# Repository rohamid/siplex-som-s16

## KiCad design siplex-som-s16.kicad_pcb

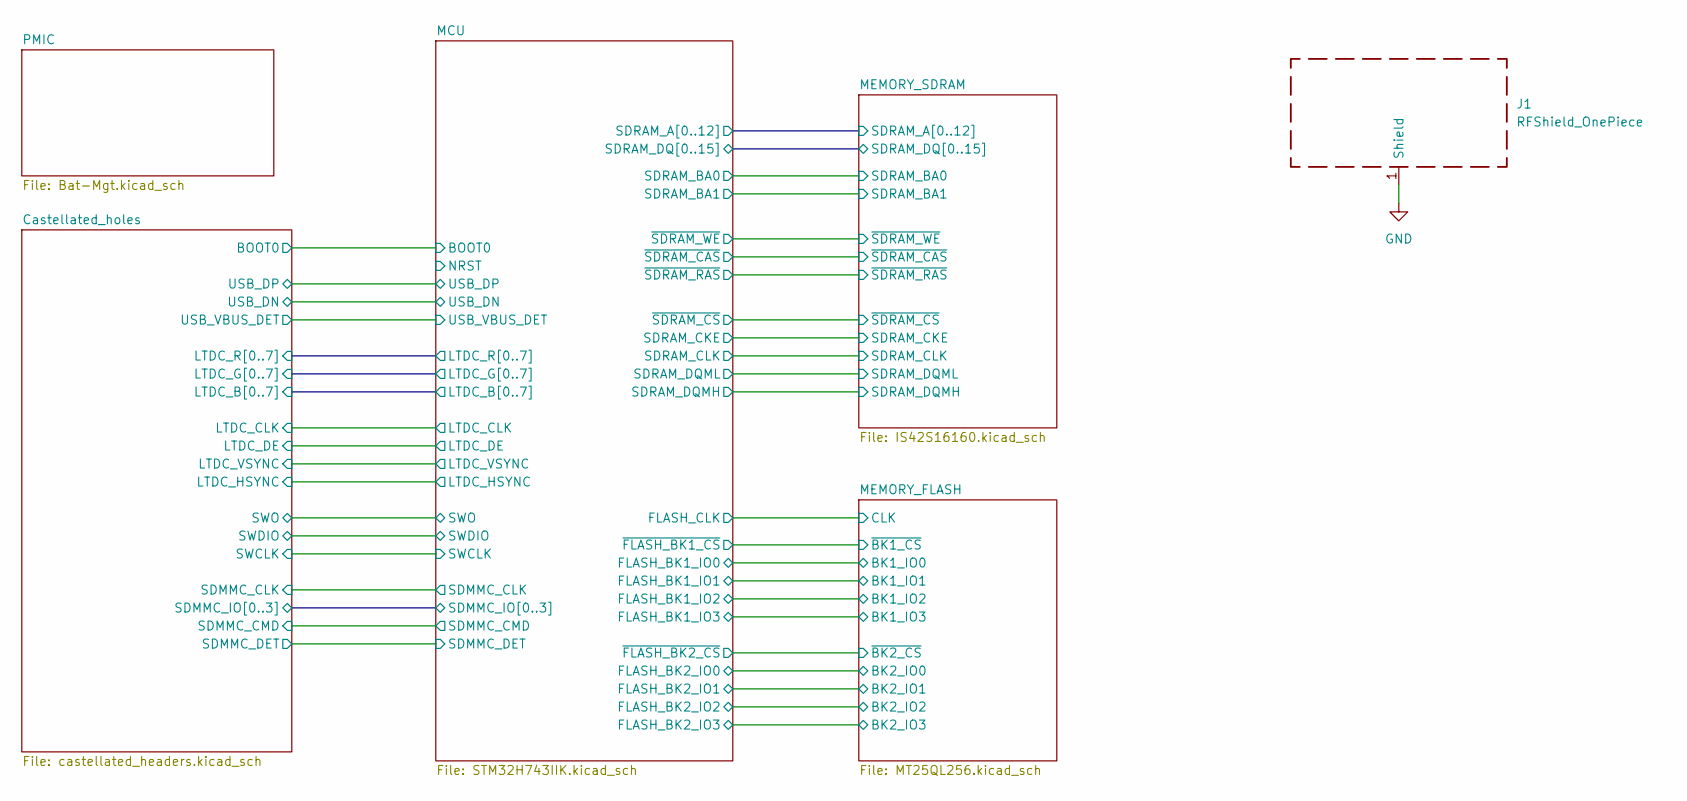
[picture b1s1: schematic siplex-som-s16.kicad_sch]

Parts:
J1: RFShield_OnePiece; Laird_Technologies_BMI-S-103_26.21x26.21mm

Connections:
GND: J1.1 (Shield); also elsewhere on the board

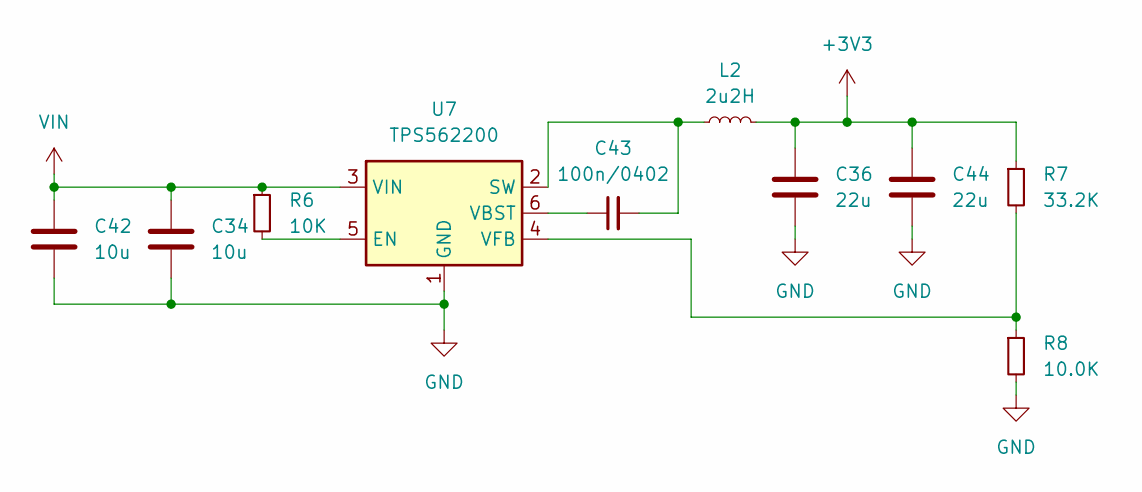
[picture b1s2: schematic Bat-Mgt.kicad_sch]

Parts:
C34, C42: 10u; C_0603_1608Metric; JLCPCB Part # C96446
C36, C44: 22u; C_0603_1608Metric; JLCPCB Part # C59461
C43: 100n/0402; C_0402_1005Metric; JLCPCB Part # C307331
L2: 2u2H; L_0805_2012Metric; JLCPCB Part # C162585
R6: 10K; R_0201_0603Metric; JLCPCB Part # C473048
R7: 33.2K; R_0402_1005Metric; JLCPCB Part # C226998
R8: 10.0K; R_0402_1005Metric; JLCPCB Part # C25804
U7: TPS562200; SOT-23-6; JLCPCB Part # C49757

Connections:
+3V3: C36.1, C44.1, L2.2, R7.1; also elsewhere on the board
GND: C34.2, C36.2, C42.2, C44.2, R8.2, U7.1 (GND); also elsewhere on the board
unnamed: R6.2, U7.5 (EN)
unnamed: C43.2, L2.1, U7.2 (SW)
unnamed: C43.1, U7.6 (VBST)
unnamed: R7.2, R8.1, U7.4 (VFB)
VIN: C34.1, C42.1, R6.1, U7.3 (VIN); also elsewhere on the board

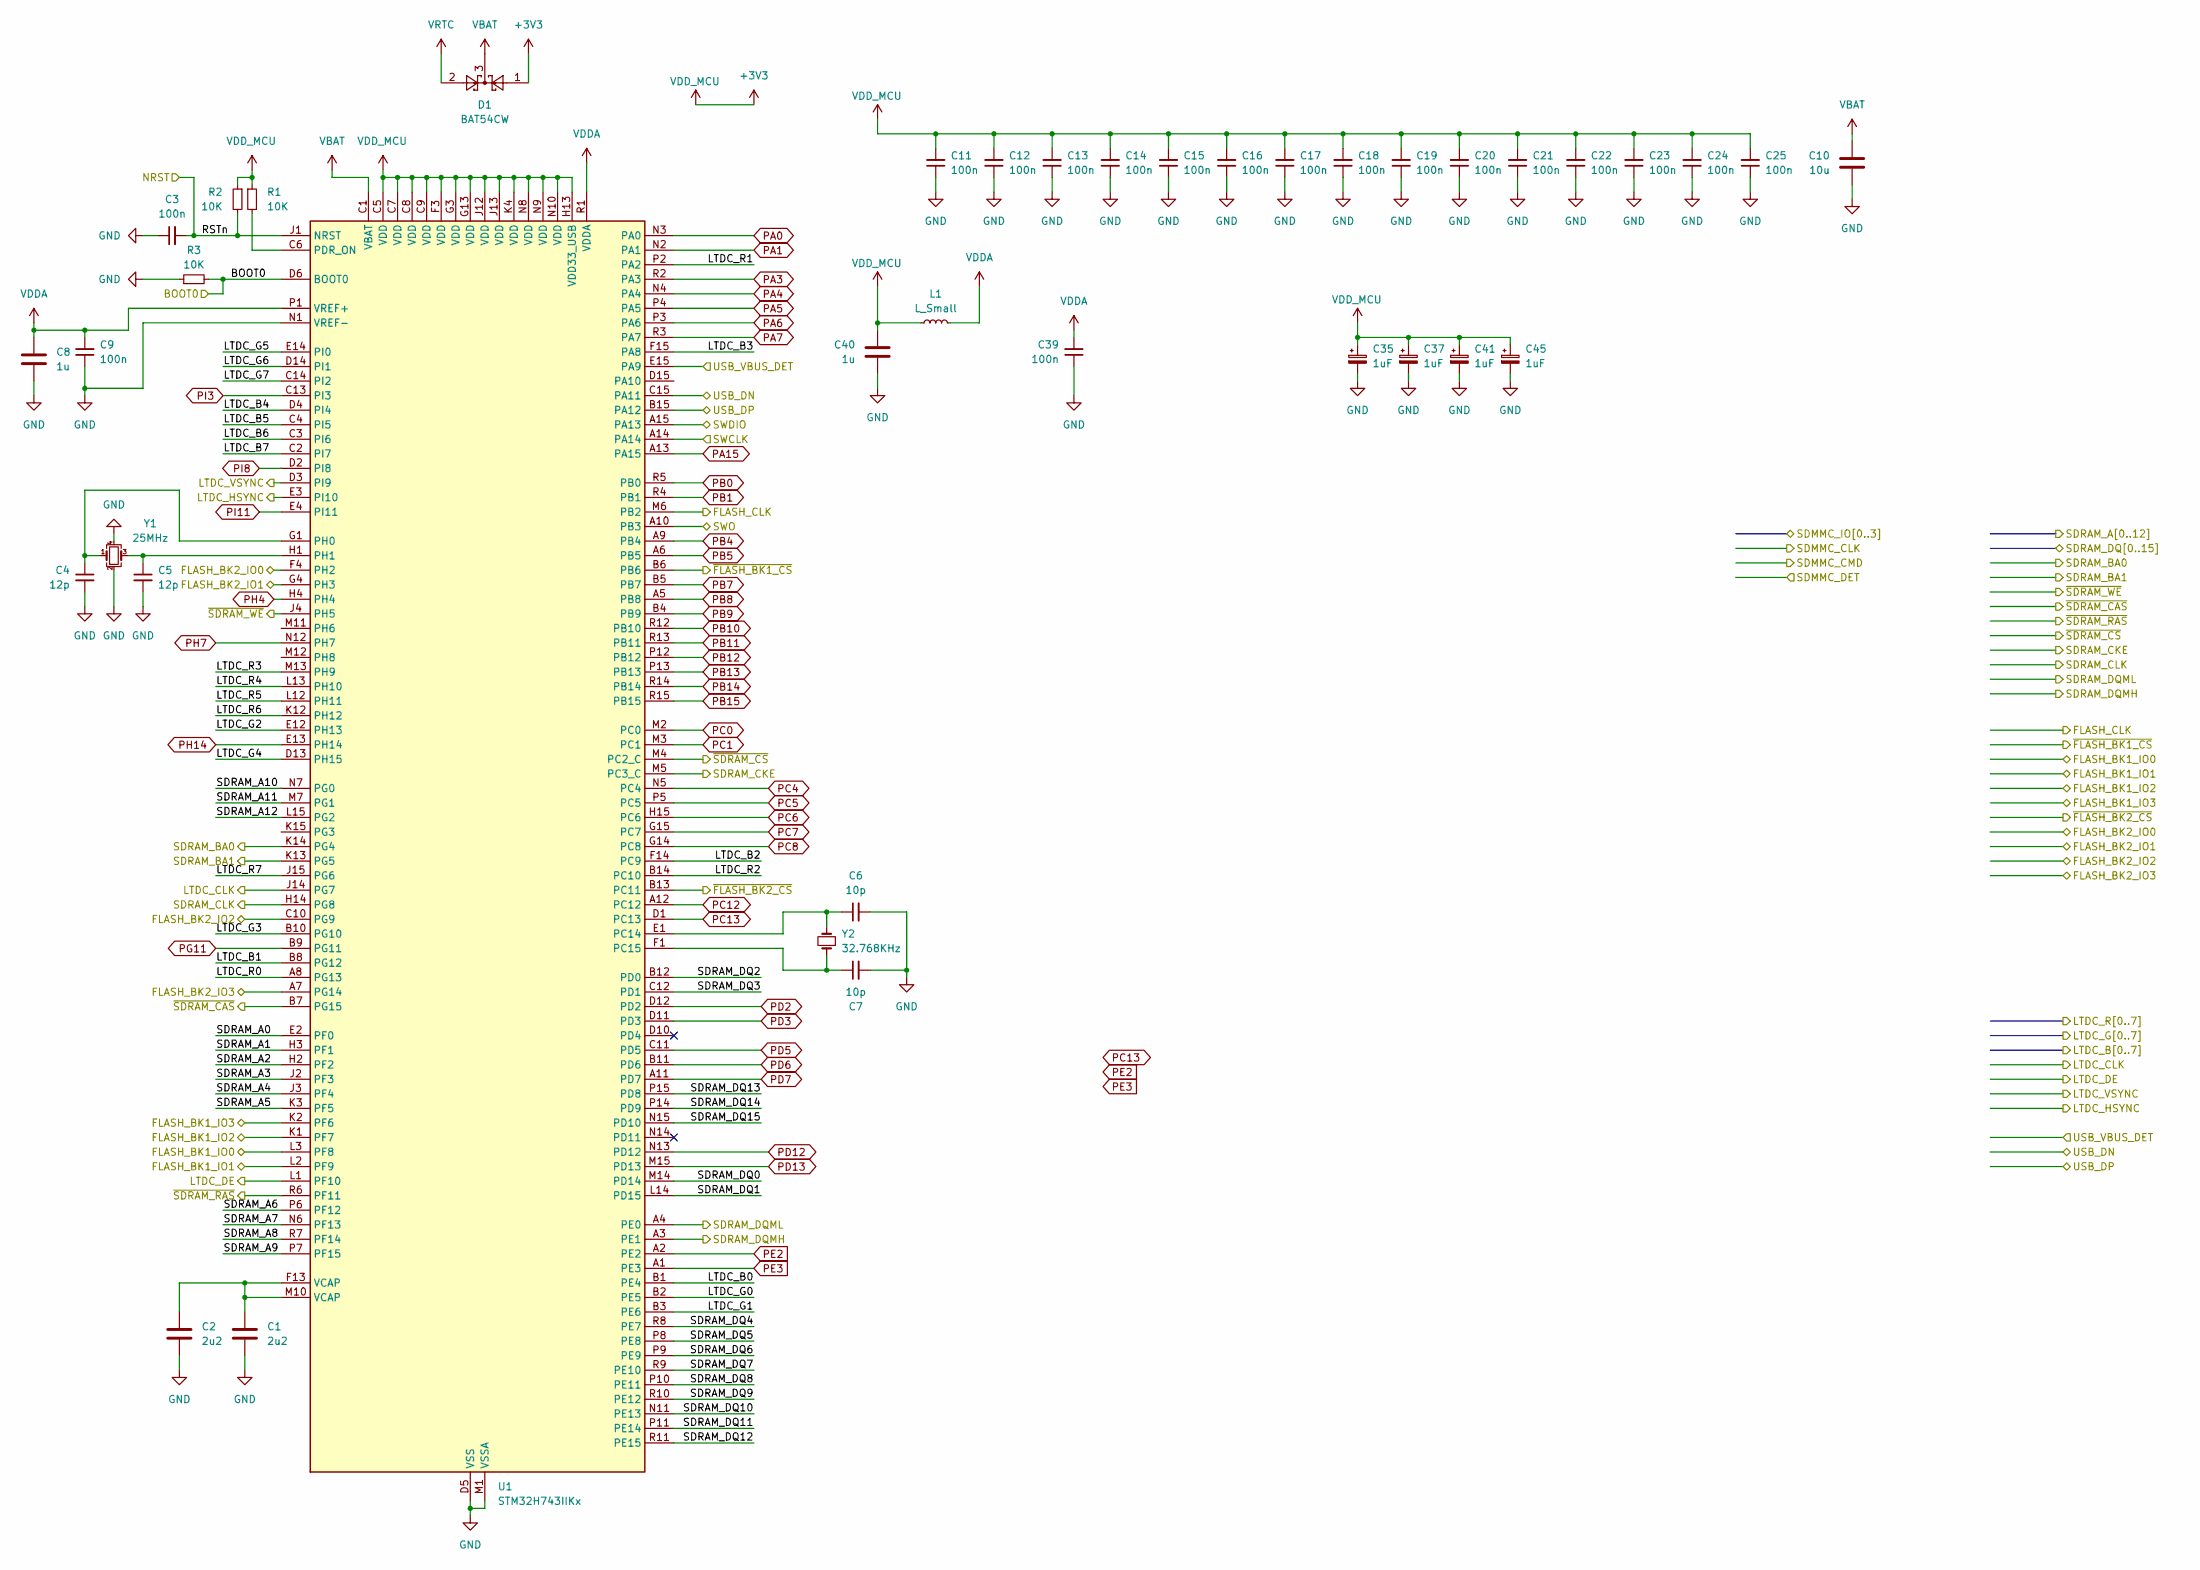
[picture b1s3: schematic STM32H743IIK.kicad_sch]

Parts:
C1, C2: 2u2; C_0402_1005Metric; JLCPCB Part # C12530
C3, C9, C11, C12, C13, C14, C15, C16, C17, C18, C19, C20, C21, C22, C23, C24, C25, C39: 100n; C_0201_0603Metric; JLCPCB Part # C307380
C4, C5: 12p; C_0201_0603Metric; JLCPCB Part # C277478
C6, C7: 10p; C_0201_0603Metric; JLCPCB Part # C76921
C8, C40: 1u; C_0402_1005Metric; JLCPCB Part # C52923
C10: 10u; C_0603_1608Metric; JLCPCB Part # C96446
C35, C37, C41, C45: 1uF; CP_EIA-1608-08_AVX-J
D1: BAT54CW; SOT-23; JLCPCB Part # C37704
L1: L_Small; L_0402_1005Metric; JLCPCB Part # C76891
R1, R2, R3: 10K; R_0201_0603Metric; JLCPCB Part # C473048
U1: STM32H743IIKx; UFBGA-201_10x10mm_Layout15x15_P0.65mm; JLCPCB Part # C129442
Y1: 25MHz; Crystal_SMD_2016-4Pin_2.0x1.6mm; JLCPCB Part # C193187
Y2: 32.768KHz; Crystal_SMD_2012-2Pin_2.0x1.2mm; JLCPCB Part # C99009

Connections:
+3V3: C11.2, C12.2, C13.2, C14.2, C15.2, C16.2, C17.2, C18.2, C19.2, C20.2, C21.2, C22.2, C23.2, C24.2, C25.2, C35.1, C37.1, C40.1, C41.1, C45.1, D1.1, L1.1, R1.1, R2.1, U1.C5 (VDD), U1.C7 (VDD), U1.C8 (VDD), U1.C9 (VDD), U1.F3 (VDD), U1.G3 (VDD), U1.G13 (VDD), U1.H13 (VDD33_USB), U1.J12 (VDD), U1.J13 (VDD), U1.K4 (VDD), U1.N8 (VDD), U1.N9 (VDD), U1.N10 (VDD); also elsewhere on the board
/Castellated_holes/LTDC_B0: U1.B1 (PE4); also elsewhere on the board
/Castellated_holes/LTDC_B1: U1.B8 (PG12); also elsewhere on the board
/Castellated_holes/LTDC_B2: U1.F14 (PC9); also elsewhere on the board
/Castellated_holes/LTDC_B3: U1.F15 (PA8); also elsewhere on the board
/Castellated_holes/LTDC_B4: U1.D4 (PI4); also elsewhere on the board
/Castellated_holes/LTDC_B5: U1.C4 (PI5); also elsewhere on the board
/Castellated_holes/LTDC_B6: U1.C3 (PI6); also elsewhere on the board
/Castellated_holes/LTDC_B7: U1.C2 (PI7); also elsewhere on the board
/Castellated_holes/LTDC_CLK: U1.J14 (PG7); also elsewhere on the board
/Castellated_holes/LTDC_DE: U1.L1 (PF10); also elsewhere on the board
/Castellated_holes/LTDC_G0: U1.B2 (PE5); also elsewhere on the board
/Castellated_holes/LTDC_G1: U1.B3 (PE6); also elsewhere on the board
/Castellated_holes/LTDC_G2: U1.E12 (PH13); also elsewhere on the board
/Castellated_holes/LTDC_G3: U1.B10 (PG10); also elsewhere on the board
/Castellated_holes/LTDC_G4: U1.D13 (PH15); also elsewhere on the board
/Castellated_holes/LTDC_G5: U1.E14 (PI0); also elsewhere on the board
/Castellated_holes/LTDC_G6: U1.D14 (PI1); also elsewhere on the board
/Castellated_holes/LTDC_G7: U1.C14 (PI2); also elsewhere on the board
/Castellated_holes/LTDC_HSYNC: U1.E3 (PI10); also elsewhere on the board
/Castellated_holes/LTDC_R0: U1.A8 (PG13); also elsewhere on the board
/Castellated_holes/LTDC_R1: U1.P2 (PA2); also elsewhere on the board
/Castellated_holes/LTDC_R2: U1.B14 (PC10); also elsewhere on the board
/Castellated_holes/LTDC_R3: U1.M13 (PH9); also elsewhere on the board
/Castellated_holes/LTDC_R4: U1.L13 (PH10); also elsewhere on the board
/Castellated_holes/LTDC_R5: U1.L12 (PH11); also elsewhere on the board
/Castellated_holes/LTDC_R6: U1.K12 (PH12); also elsewhere on the board
/Castellated_holes/LTDC_R7: U1.J15 (PG6); also elsewhere on the board
/Castellated_holes/LTDC_VSYNC: U1.D3 (PI9); also elsewhere on the board
/Castellated_holes/SWCLK: U1.A14; also elsewhere on the board
/Castellated_holes/SWDIO: U1.A15 (PA13); also elsewhere on the board
/Castellated_holes/SWO: U1.A10 (PB3); also elsewhere on the board
/Castellated_holes/USB_DN: U1.C15 (PA11); also elsewhere on the board
/Castellated_holes/USB_DP: U1.B15 (PA12); also elsewhere on the board
/Castellated_holes/USB_VBUS_DET: U1.E15 (PA9); also elsewhere on the board
/MCU/BOOT0: R3.2, U1.D6 (BOOT0); also elsewhere on the board
/MCU/FLASH_BK1_IO0: U1.L3 (PF8); also elsewhere on the board
/MCU/FLASH_BK1_IO1: U1.L2 (PF9); also elsewhere on the board
/MCU/FLASH_BK1_IO2: U1.K1 (PF7); also elsewhere on the board
/MCU/FLASH_BK1_IO3: U1.K2 (PF6); also elsewhere on the board
/MCU/FLASH_BK2_IO0: U1.F4 (PH2); also elsewhere on the board
/MCU/FLASH_BK2_IO1: U1.G4 (PH3); also elsewhere on the board
/MCU/FLASH_BK2_IO2: U1.C10 (PG9); also elsewhere on the board
/MCU/FLASH_BK2_IO3: U1.A7 (PG14); also elsewhere on the board
/MCU/FLASH_CLK: U1.M6 (PB2); also elsewhere on the board
/MCU/RSTn: C3.2, R2.2, U1.J1 (NRST)
/MCU/SDRAM_A0: U1.E2 (PF0); also elsewhere on the board
/MCU/SDRAM_A1: U1.H3 (PF1); also elsewhere on the board
/MCU/SDRAM_A2: U1.H2 (PF2); also elsewhere on the board
/MCU/SDRAM_A3: U1.J2 (PF3); also elsewhere on the board
/MCU/SDRAM_A4: U1.J3 (PF4); also elsewhere on the board
/MCU/SDRAM_A5: U1.K3 (PF5); also elsewhere on the board
/MCU/SDRAM_A6: U1.P6 (PF12); also elsewhere on the board
/MCU/SDRAM_A7: U1.N6 (PF13); also elsewhere on the board
/MCU/SDRAM_A8: U1.R7 (PF14); also elsewhere on the board
/MCU/SDRAM_A9: U1.P7 (PF15); also elsewhere on the board
/MCU/SDRAM_A10: U1.N7 (PG0); also elsewhere on the board
/MCU/SDRAM_A11: U1.M7 (PG1); also elsewhere on the board
/MCU/SDRAM_A12: U1.L15 (PG2); also elsewhere on the board
/MCU/SDRAM_BA0: U1.K14 (PG4); also elsewhere on the board
/MCU/SDRAM_BA1: U1.K13 (PG5); also elsewhere on the board
/MCU/SDRAM_CKE: U1.M5 (PC3_C); also elsewhere on the board
/MCU/SDRAM_CLK: U1.H14 (PG8); also elsewhere on the board
/MCU/SDRAM_DQ0: U1.M14 (PD14); also elsewhere on the board
/MCU/SDRAM_DQ1: U1.L14 (PD15); also elsewhere on the board
/MCU/SDRAM_DQ2: U1.B12 (PD0); also elsewhere on the board
/MCU/SDRAM_DQ3: U1.C12 (PD1); also elsewhere on the board
/MCU/SDRAM_DQ4: U1.R8 (PE7); also elsewhere on the board
/MCU/SDRAM_DQ5: U1.P8 (PE8); also elsewhere on the board
/MCU/SDRAM_DQ6: U1.P9 (PE9); also elsewhere on the board
/MCU/SDRAM_DQ7: U1.R9 (PE10); also elsewhere on the board
/MCU/SDRAM_DQ8: U1.P10 (PE11); also elsewhere on the board
/MCU/SDRAM_DQ9: U1.R10 (PE12); also elsewhere on the board
/MCU/SDRAM_DQ10: U1.N11 (PE13); also elsewhere on the board
/MCU/SDRAM_DQ11: U1.P11 (PE14); also elsewhere on the board
/MCU/SDRAM_DQ12: U1.R11 (PE15); also elsewhere on the board
/MCU/SDRAM_DQ13: U1.P15 (PD8); also elsewhere on the board
/MCU/SDRAM_DQ14: U1.P14 (PD9); also elsewhere on the board
/MCU/SDRAM_DQ15: U1.N15 (PD10); also elsewhere on the board
/MCU/SDRAM_DQMH: U1.A3 (PE1); also elsewhere on the board
/MCU/SDRAM_DQML: U1.A4 (PE0); also elsewhere on the board
/MCU/~FLASH_BK1_CS: U1.B6; also elsewhere on the board
/MCU/~FLASH_BK2_CS: U1.B13 (PC11); also elsewhere on the board
/MCU/~SDRAM_CAS: U1.B7 (PG15); also elsewhere on the board
/MCU/~SDRAM_CS: U1.M4 (PC2_C); also elsewhere on the board
/MCU/~SDRAM_RAS: U1.R6 (PF11); also elsewhere on the board
/MCU/~SDRAM_WE: U1.J4 (PH5); also elsewhere on the board
GND: C1.2, C2.2, C3.1, C4.2, C5.2, C6.2, C7.2, C8.2, C9.1, C10.2, C11.1, C12.1, C13.1, C14.1, C15.1, C16.1, C17.1, C18.1, C19.1, C20.1, C21.1, C22.1, C23.1, C24.1, C25.1, C35.2, C37.2, C39.1, C40.2, C41.2, C45.2, R3.1, U1.D5 (VSS), U1.D7 (VSS), U1.D8 (VSS), U1.D9 (VSS), U1.F2 (VSS), U1.F6 (VSS), U1.F7 (VSS), U1.F8 (VSS), U1.F9 (VSS), U1.F10 (VSS), U1.F12 (VSS), U1.G2 (VSS), U1.G6 (VSS), U1.G7 (VSS), U1.G8 (VSS), U1.G9 (VSS), U1.G10 (VSS), U1.G12 (VSS), U1.H6 (VSS), U1.H7 (VSS), U1.H8 (VSS), U1.H9 (VSS), U1.H10 (VSS), U1.H12 (VSS), U1.J6 (VSS), U1.J7 (VSS), U1.J8 (VSS), U1.J9 (VSS), U1.J10 (VSS), U1.K6 (VSS), U1.K7 (VSS), U1.K8 (VSS), U1.K9 (VSS), U1.K10 (VSS), U1.L4 (VSS), U1.M1 (VSSA), U1.M8 (VSS), U1.M9 (VSS), U1.N1 (VREF-), Y1.2, Y1.4; also elsewhere on the board
unnamed: C1.1, C2.1, U1.F13 (VCAP), U1.M10 (VCAP)
unnamed: C6.1, U1.E1 (PC14), Y2.2
unnamed: C7.1, U1.F1 (PC15), Y2.1
unnamed: R1.2, U1.C6 (PDR_ON)
unnamed: C4.1, U1.G1 (PH0), Y1.1
unnamed: C5.1, U1.H1, Y1.3
PA0: U1.N3 (PA0); also elsewhere on the board
PA1: U1.N2 (PA1); also elsewhere on the board
PA3: U1.R2 (PA3); also elsewhere on the board
PA4: U1.N4 (PA4); also elsewhere on the board
PA5: U1.P4 (PA5); also elsewhere on the board
PA6: U1.P3 (PA6); also elsewhere on the board
PA7: U1.R3 (PA7); also elsewhere on the board
PA15: U1.A13 (PA15); also elsewhere on the board
PB0: U1.R5 (PB0); also elsewhere on the board
PB1: U1.R4 (PB1); also elsewhere on the board
PB4: U1.A9 (PB4); also elsewhere on the board
PB5: U1.A6 (PB5); also elsewhere on the board
PB7: U1.B5 (PB7); also elsewhere on the board
PB8: U1.A5 (PB8); also elsewhere on the board
PB9: U1.B4 (PB9); also elsewhere on the board
PB10: U1.R12 (PB10); also elsewhere on the board
PB11: U1.R13 (PB11); also elsewhere on the board
PB12: U1.P12 (PB12); also elsewhere on the board
PB13: U1.P13 (PB13); also elsewhere on the board
PB14: U1.R14 (PB14); also elsewhere on the board
PB15: U1.R15 (PB15); also elsewhere on the board
PC0: U1.M2 (PC0); also elsewhere on the board
PC1: U1.M3 (PC1); also elsewhere on the board
PC4: U1.N5 (PC4); also elsewhere on the board
PC5: U1.P5 (PC5); also elsewhere on the board
PC6: U1.H15 (PC6); also elsewhere on the board
PC7: U1.G15 (PC7); also elsewhere on the board
PC8: U1.G14 (PC8); also elsewhere on the board
PC12: U1.A12 (PC12); also elsewhere on the board
PC13: U1.D1 (PC13)
PD2: U1.D12 (PD2); also elsewhere on the board
PD3: U1.D11 (PD3); also elsewhere on the board
PD5: U1.C11 (PD5); also elsewhere on the board
PD6: U1.B11 (PD6); also elsewhere on the board
PD7: U1.A11 (PD7); also elsewhere on the board
PD12: U1.N13 (PD12); also elsewhere on the board
PD13: U1.M15 (PD13); also elsewhere on the board
PE2: U1.A2 (PE2)
PE3: U1.A1 (PE3)
PG11: U1.B9 (PG11); also elsewhere on the board
PH4: U1.H4; also elsewhere on the board
PH7: U1.N12 (PH7); also elsewhere on the board
PH14: U1.E13 (PH14); also elsewhere on the board
PI3: U1.C13 (PI3); also elsewhere on the board
PI8: U1.D2 (PI8)
PI11: U1.E4 (PI11)
VBAT: C10.1, D1.3, U1.C1 (VBAT)
VDDA: C8.1, C9.2, C39.2, L1.2, U1.P1 (VREF+), U1.R1 (VDDA)
VRTC: D1.2; also elsewhere on the board

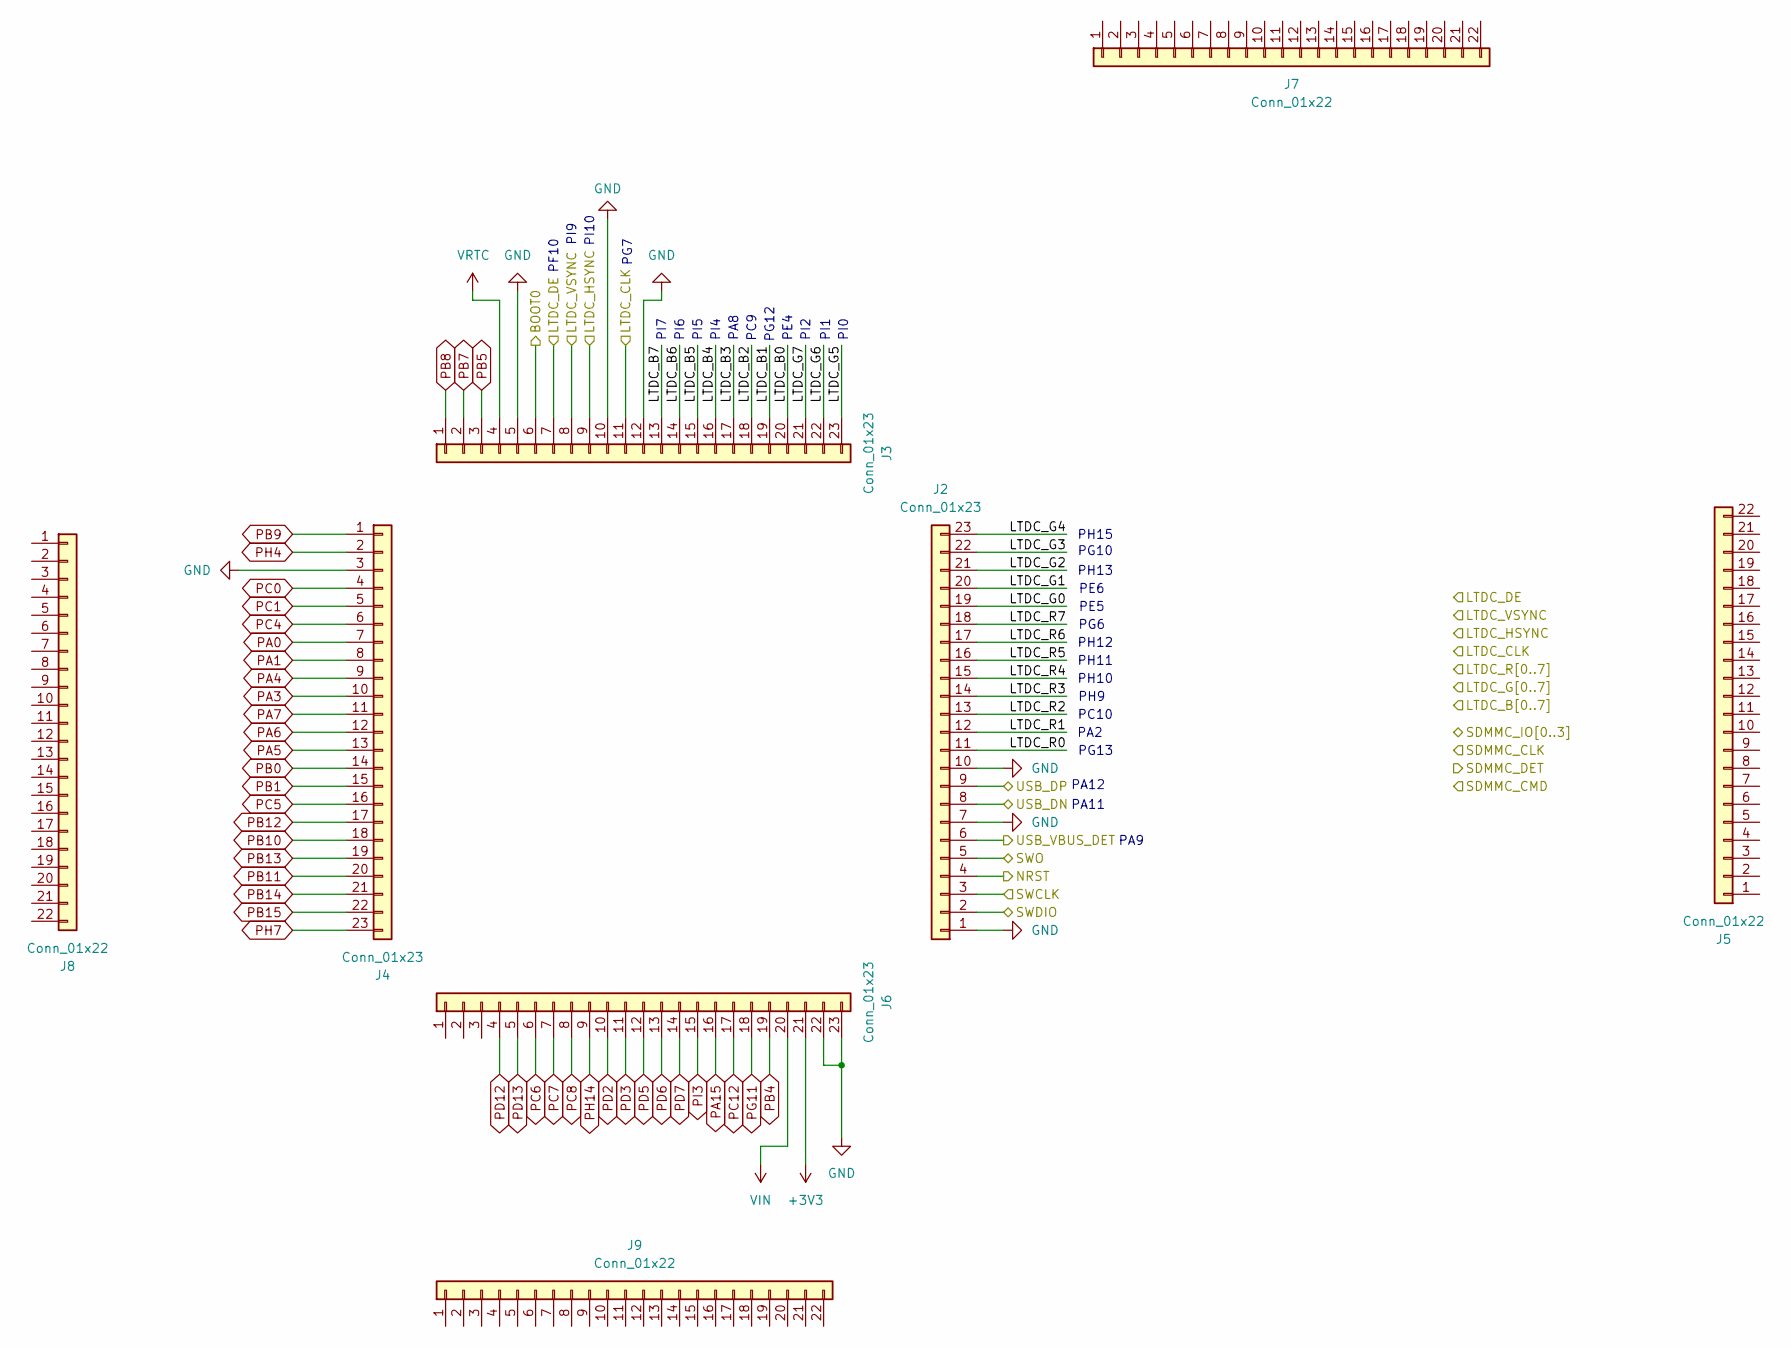
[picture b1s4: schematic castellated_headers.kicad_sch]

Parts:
J2, J3, J4, J6: Conn_01x23; castellated_01x23_P1.2mm
J5, J7, J8, J9: Conn_01x22; castellated_01x22_P1.27mm

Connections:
+3V3: J6.21; also elsewhere on the board
/Castellated_holes/LTDC_B0: J3.20; also elsewhere on the board
/Castellated_holes/LTDC_B1: J3.19; also elsewhere on the board
/Castellated_holes/LTDC_B2: J3.18; also elsewhere on the board
/Castellated_holes/LTDC_B3: J3.17; also elsewhere on the board
/Castellated_holes/LTDC_B4: J3.16; also elsewhere on the board
/Castellated_holes/LTDC_B5: J3.15; also elsewhere on the board
/Castellated_holes/LTDC_B6: J3.14; also elsewhere on the board
/Castellated_holes/LTDC_B7: J3.13; also elsewhere on the board
/Castellated_holes/LTDC_CLK: J3.11; also elsewhere on the board
/Castellated_holes/LTDC_DE: J3.7; also elsewhere on the board
/Castellated_holes/LTDC_G0: J2.19; also elsewhere on the board
/Castellated_holes/LTDC_G1: J2.20; also elsewhere on the board
/Castellated_holes/LTDC_G2: J2.21; also elsewhere on the board
/Castellated_holes/LTDC_G3: J2.22; also elsewhere on the board
/Castellated_holes/LTDC_G4: J2.23; also elsewhere on the board
/Castellated_holes/LTDC_G5: J3.23; also elsewhere on the board
/Castellated_holes/LTDC_G6: J3.22; also elsewhere on the board
/Castellated_holes/LTDC_G7: J3.21; also elsewhere on the board
/Castellated_holes/LTDC_HSYNC: J3.9; also elsewhere on the board
/Castellated_holes/LTDC_R0: J2.11; also elsewhere on the board
/Castellated_holes/LTDC_R1: J2.12; also elsewhere on the board
/Castellated_holes/LTDC_R2: J2.13; also elsewhere on the board
/Castellated_holes/LTDC_R3: J2.14; also elsewhere on the board
/Castellated_holes/LTDC_R4: J2.15; also elsewhere on the board
/Castellated_holes/LTDC_R5: J2.16; also elsewhere on the board
/Castellated_holes/LTDC_R6: J2.17; also elsewhere on the board
/Castellated_holes/LTDC_R7: J2.18; also elsewhere on the board
/Castellated_holes/LTDC_VSYNC: J3.8; also elsewhere on the board
/Castellated_holes/NRST: J2.4
/Castellated_holes/SWCLK: J2.3; also elsewhere on the board
/Castellated_holes/SWDIO: J2.2; also elsewhere on the board
/Castellated_holes/SWO: J2.5; also elsewhere on the board
/Castellated_holes/USB_DN: J2.8; also elsewhere on the board
/Castellated_holes/USB_DP: J2.9; also elsewhere on the board
/Castellated_holes/USB_VBUS_DET: J2.6; also elsewhere on the board
/MCU/BOOT0: J3.6; also elsewhere on the board
GND: J2.1, J2.7, J2.10, J3.5, J3.10, J3.12, J4.3, J6.22, J6.23; also elsewhere on the board
PA0: J4.7; also elsewhere on the board
PA1: J4.8; also elsewhere on the board
PA3: J4.10; also elsewhere on the board
PA4: J4.9; also elsewhere on the board
PA5: J4.13; also elsewhere on the board
PA6: J4.12; also elsewhere on the board
PA7: J4.11; also elsewhere on the board
PA15: J6.16; also elsewhere on the board
PB0: J4.14; also elsewhere on the board
PB1: J4.15; also elsewhere on the board
PB4: J6.19; also elsewhere on the board
PB5: J3.3; also elsewhere on the board
PB7: J3.2; also elsewhere on the board
PB8: J3.1; also elsewhere on the board
PB9: J4.1; also elsewhere on the board
PB10: J4.18; also elsewhere on the board
PB11: J4.20; also elsewhere on the board
PB12: J4.17; also elsewhere on the board
PB13: J4.19; also elsewhere on the board
PB14: J4.21; also elsewhere on the board
PB15: J4.22; also elsewhere on the board
PC0: J4.4; also elsewhere on the board
PC1: J4.5; also elsewhere on the board
PC4: J4.6; also elsewhere on the board
PC5: J4.16; also elsewhere on the board
PC6: J6.6; also elsewhere on the board
PC7: J6.7; also elsewhere on the board
PC8: J6.8; also elsewhere on the board
PC12: J6.17; also elsewhere on the board
PD2: J6.10; also elsewhere on the board
PD3: J6.11; also elsewhere on the board
PD5: J6.12; also elsewhere on the board
PD6: J6.13; also elsewhere on the board
PD7: J6.14; also elsewhere on the board
PD12: J6.4; also elsewhere on the board
PD13: J6.5; also elsewhere on the board
PG11: J6.18; also elsewhere on the board
PH4: J4.2; also elsewhere on the board
PH7: J4.23; also elsewhere on the board
PH14: J6.9; also elsewhere on the board
PI3: J6.15; also elsewhere on the board
VIN: J6.20; also elsewhere on the board
VRTC: J3.4; also elsewhere on the board

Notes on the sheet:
PC10
PI1
PA9
PI6
PG12
PF10
PI7
PI9
PA11
PA12
PG10
PI5
PG7
PI10
PH11
PH15
PI4
PG13
PC9
PH9
PI2
PH13
PA2
PH12
PH10
PA8
PE5
PE4
PI0
PG6
PE6

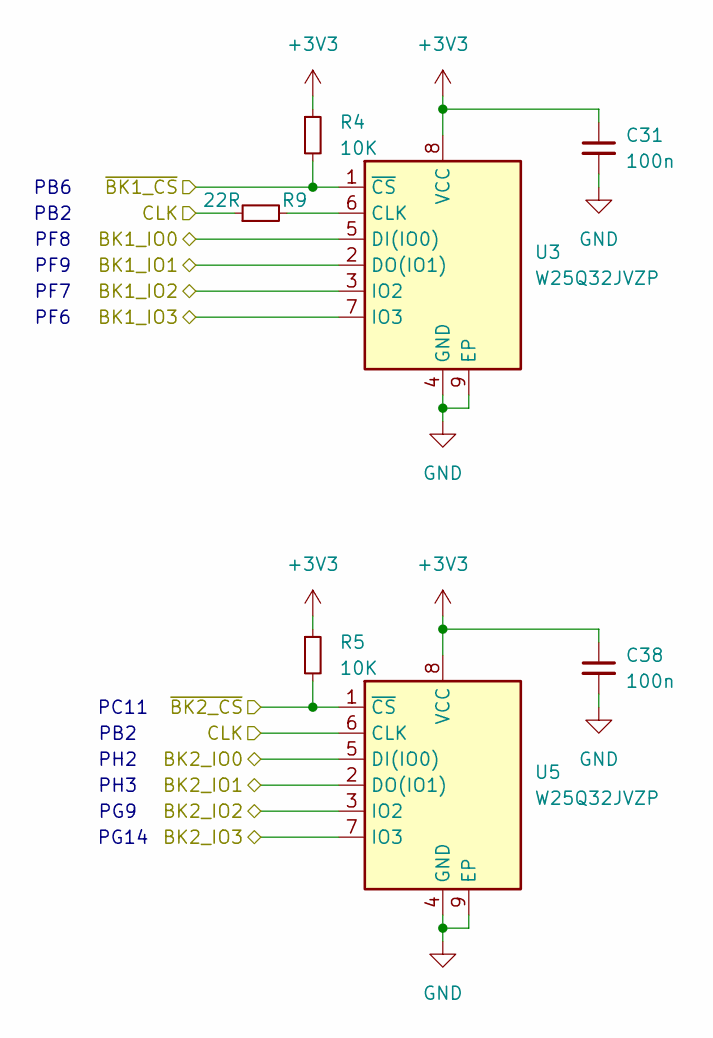
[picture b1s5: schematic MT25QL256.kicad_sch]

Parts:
C31, C38: 100n; C_0201_0603Metric; JLCPCB Part # C307380
R4, R5: 10K; R_0201_0603Metric; JLCPCB Part # C473048
R9: 22R; R_0201_0603Metric; JLCPCB Part # C473048
U3, U5: W25Q32JVZP; SON127P800X600X80-9N; JLCPCB Part # C2986165

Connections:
+3V3: C31.1, C38.1, R4.1, R5.1, U3.8 (VCC), U5.8 (VCC); also elsewhere on the board
/MCU/FLASH_BK1_IO0: U3.5 (DI(IO0)); also elsewhere on the board
/MCU/FLASH_BK1_IO1: U3.2 (DO(IO1)); also elsewhere on the board
/MCU/FLASH_BK1_IO2: U3.3 (IO2); also elsewhere on the board
/MCU/FLASH_BK1_IO3: U3.7 (IO3); also elsewhere on the board
/MCU/FLASH_BK2_IO0: U5.5 (DI(IO0)); also elsewhere on the board
/MCU/FLASH_BK2_IO1: U5.2 (DO(IO1)); also elsewhere on the board
/MCU/FLASH_BK2_IO2: U5.3 (IO2); also elsewhere on the board
/MCU/FLASH_BK2_IO3: U5.7 (IO3); also elsewhere on the board
/MCU/FLASH_CLK: R9.1, U5.6 (CLK); also elsewhere on the board
/MCU/~FLASH_BK1_CS: R4.2, U3.1 (~CS); also elsewhere on the board
/MCU/~FLASH_BK2_CS: R5.2, U5.1 (~CS); also elsewhere on the board
GND: C31.2, C38.2, U3.4 (GND), U3.9 (EP), U5.4 (GND), U5.9 (EP); also elsewhere on the board
unnamed: R9.2, U3.6 (CLK)

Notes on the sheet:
PB6
PB2
PF7
PF8
PG9
PF6
PG14
PH3
PC11
PF9
PH2

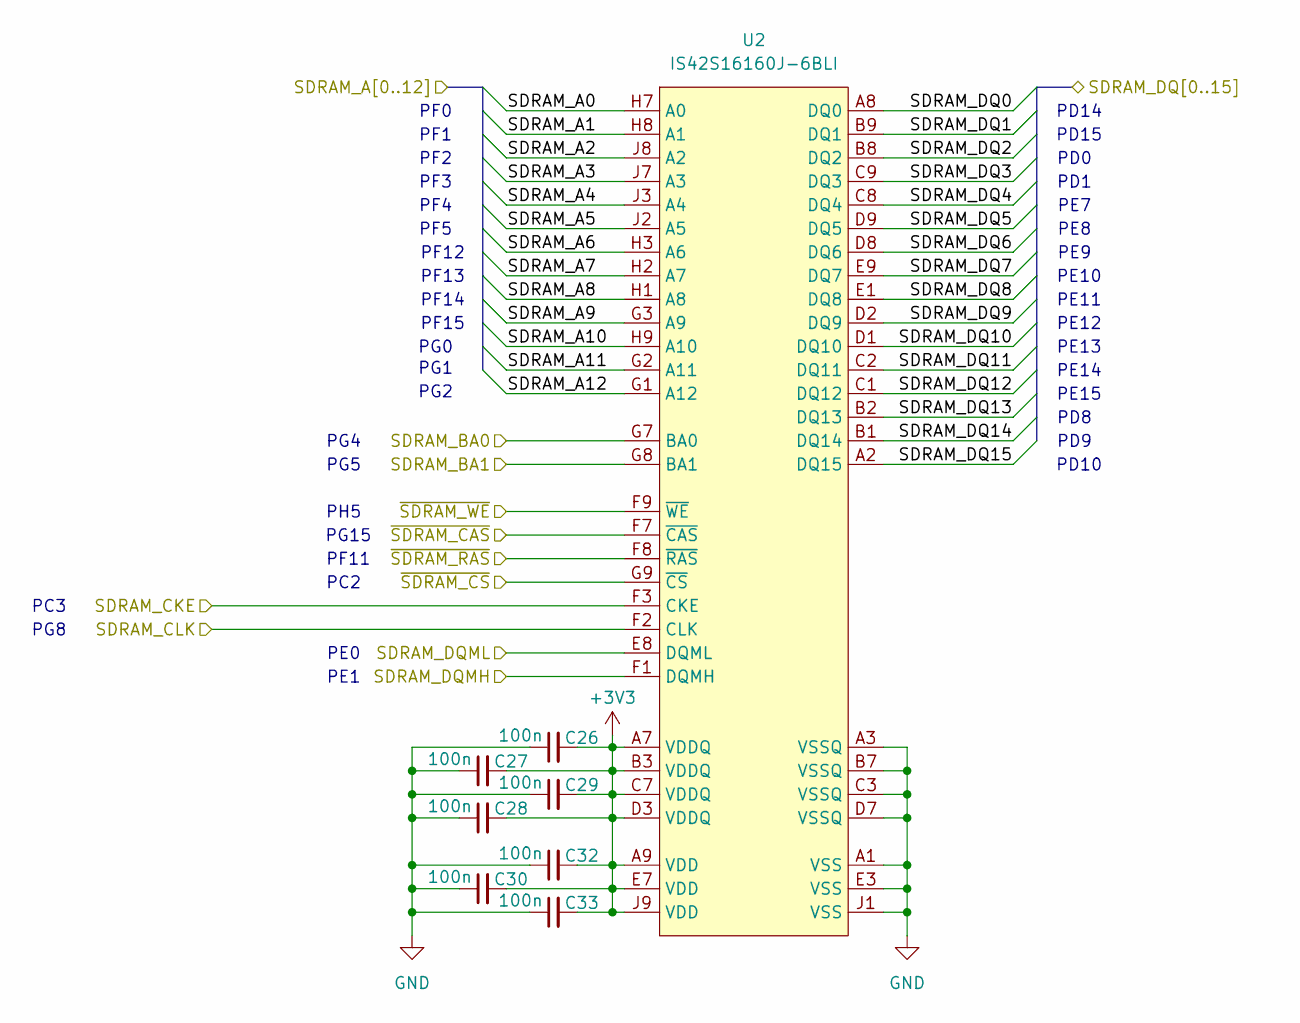
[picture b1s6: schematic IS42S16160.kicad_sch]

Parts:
C26, C27, C28, C29, C30, C32, C33: 100n; C_0201_0603Metric; JLCPCB Part # C307380
U2: IS42S16160J-6BLI; Alliance_TFBGA-54_8x8mm_Layout9x9_P0.8mm; JLCPCB Part # C1348766

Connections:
+3V3: C26.2, C27.2, C28.2, C29.2, C30.2, C32.2, C33.2, U2.A7 (VDDQ), U2.A9 (VDD), U2.B3 (VDDQ), U2.C7 (VDDQ), U2.D3 (VDDQ), U2.E7 (VDD), U2.J9 (VDD); also elsewhere on the board
/MCU/SDRAM_A0: U2.H7 (A0); also elsewhere on the board
/MCU/SDRAM_A1: U2.H8 (A1); also elsewhere on the board
/MCU/SDRAM_A2: U2.J8 (A2); also elsewhere on the board
/MCU/SDRAM_A3: U2.J7 (A3); also elsewhere on the board
/MCU/SDRAM_A4: U2.J3 (A4); also elsewhere on the board
/MCU/SDRAM_A5: U2.J2 (A5); also elsewhere on the board
/MCU/SDRAM_A6: U2.H3 (A6); also elsewhere on the board
/MCU/SDRAM_A7: U2.H2 (A7); also elsewhere on the board
/MCU/SDRAM_A8: U2.H1 (A8); also elsewhere on the board
/MCU/SDRAM_A9: U2.G3 (A9); also elsewhere on the board
/MCU/SDRAM_A10: U2.H9 (A10); also elsewhere on the board
/MCU/SDRAM_A11: U2.G2 (A11); also elsewhere on the board
/MCU/SDRAM_A12: U2.G1 (A12); also elsewhere on the board
/MCU/SDRAM_BA0: U2.G7 (BA0); also elsewhere on the board
/MCU/SDRAM_BA1: U2.G8 (BA1); also elsewhere on the board
/MCU/SDRAM_CKE: U2.F3 (CKE); also elsewhere on the board
/MCU/SDRAM_CLK: U2.F2 (CLK); also elsewhere on the board
/MCU/SDRAM_DQ0: U2.A8 (DQ0); also elsewhere on the board
/MCU/SDRAM_DQ1: U2.B9 (DQ1); also elsewhere on the board
/MCU/SDRAM_DQ2: U2.B8 (DQ2); also elsewhere on the board
/MCU/SDRAM_DQ3: U2.C9 (DQ3); also elsewhere on the board
/MCU/SDRAM_DQ4: U2.C8 (DQ4); also elsewhere on the board
/MCU/SDRAM_DQ5: U2.D9 (DQ5); also elsewhere on the board
/MCU/SDRAM_DQ6: U2.D8 (DQ6); also elsewhere on the board
/MCU/SDRAM_DQ7: U2.E9 (DQ7); also elsewhere on the board
/MCU/SDRAM_DQ8: U2.E1 (DQ8); also elsewhere on the board
/MCU/SDRAM_DQ9: U2.D2 (DQ9); also elsewhere on the board
/MCU/SDRAM_DQ10: U2.D1 (DQ10); also elsewhere on the board
/MCU/SDRAM_DQ11: U2.C2 (DQ11); also elsewhere on the board
/MCU/SDRAM_DQ12: U2.C1 (DQ12); also elsewhere on the board
/MCU/SDRAM_DQ13: U2.B2 (DQ13); also elsewhere on the board
/MCU/SDRAM_DQ14: U2.B1 (DQ14); also elsewhere on the board
/MCU/SDRAM_DQ15: U2.A2 (DQ15); also elsewhere on the board
/MCU/SDRAM_DQMH: U2.F1 (DQMH); also elsewhere on the board
/MCU/SDRAM_DQML: U2.E8 (DQML); also elsewhere on the board
/MCU/~SDRAM_CAS: U2.F7 (~CAS); also elsewhere on the board
/MCU/~SDRAM_CS: U2.G9 (~CS); also elsewhere on the board
/MCU/~SDRAM_RAS: U2.F8 (~RAS); also elsewhere on the board
/MCU/~SDRAM_WE: U2.F9 (~WE); also elsewhere on the board
GND: C26.1, C27.1, C28.1, C29.1, C30.1, C32.1, C33.1, U2.A1 (VSS), U2.A3 (VSSQ), U2.B7 (VSSQ), U2.C3 (VSSQ), U2.D7 (VSSQ), U2.E3 (VSS), U2.J1 (VSS); also elsewhere on the board

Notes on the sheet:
PE15
PD9
PD0
PF0
PE8
PF1
PE9
PG1
PC2
PF5
PG5
PE0
PD10
PF14
PE12
PF15
PD1
PG4
PG8
PC3
PD8
PE13
PF13
PF4
PD14
PF11
PF12
PG0
PE1
PH5
PG2
PE14
PD15
PF3
PG15
PE10
PE11
PF2
PE7

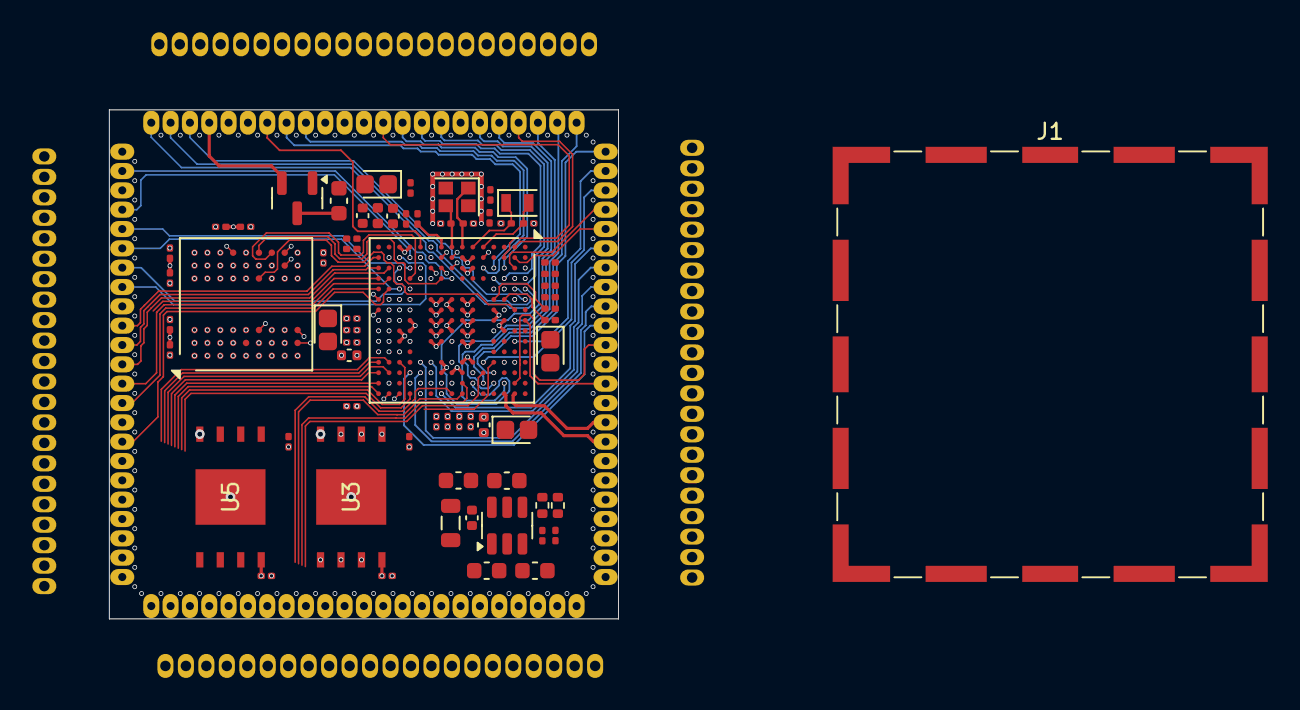
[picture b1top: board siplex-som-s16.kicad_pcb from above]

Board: 8 copper layers, 31.6 x 31.6 mm, 73 parts (0 on the bottom side), 144 nets.

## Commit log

2024-08-26 remove Windows's specific error log file
2024-08-26 Add power
2024-08-28 Change to 8 layer, doing SDRAM traces
2024-08-29 Finished SDRAM, QSPI FLASH (trace length not matched yet)
2024-08-30 Change to via-in-pad mode
2024-09-02 Finished SDRAM_DATA
2024-09-03 Finished SDRAM_ADDRESS
2024-09-04 Modify SDRAM tracks as its conflicted with FLASH tracks
2024-09-04 Finished FLASH tracks
2024-09-04 Finished LTDC tracks
2024-09-05 test remote connection
2024-09-09 Finished fanout all remaining pin, Power block left
2024-09-10 Changed PMIC to dc-dc converter, finished track
2024-09-13 generate doc
2024-10-01 98% finished, st-link part left
2024-10-03 Change LCD CLK, VSYNC, HSYNC, to be match with the position of standard 40 pin LCD module
2024-10-13 Adding JLCPCB Part #
2025-06-04 Optimize layout with lowest impedance as possible
2025-06-09 SDRAM finished, changed castellated to 23pin each side, few pins unconnected
